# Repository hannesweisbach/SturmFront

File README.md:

# SturmFront

SturmFront is a DIY fan-controller for indoor sports, which adjusts fan speed according to your current heart rate.

Commercially available is the Wahoo® KICKR Headwind, which has an integrated fan and regulates fan speed according to your power output. Keith Wakeham developed an open-source DIY fan controller named [Maelstom](https://github.com/kwakeham/Maelstrom). Maelstrom also adjusts fan speed according to your power output.

I developed SturmFront independently. A project description is also available: [https://hannesweisbach.github.io/SturmFront/](https://hannesweisbach.github.io/SturmFront/)

## Software used

I used KiCAD as EDA-tool. The controller is based on the Nordic Semiconductor [NRF52832 SoC](https://www.nordicsemi.com/products/nrf52832). I used the [NRF5 SDK 17.1.0](https://www.nordicsemi.com/Products/Development-software/nrf5-sdk/download) in conjuction with the [S332 softdevice](https://www.nordicsemi.com/Products/Development-software/s332-ant) to provide ANT+ and BLE connectivity.

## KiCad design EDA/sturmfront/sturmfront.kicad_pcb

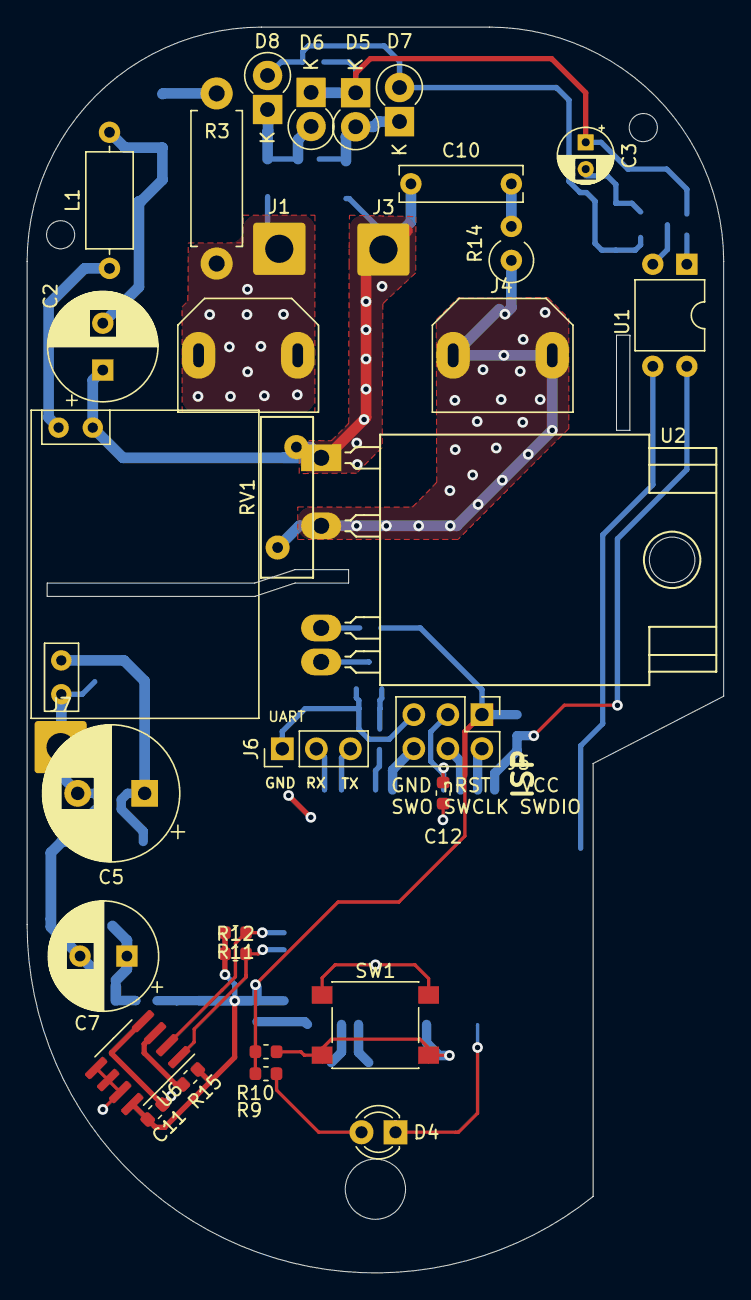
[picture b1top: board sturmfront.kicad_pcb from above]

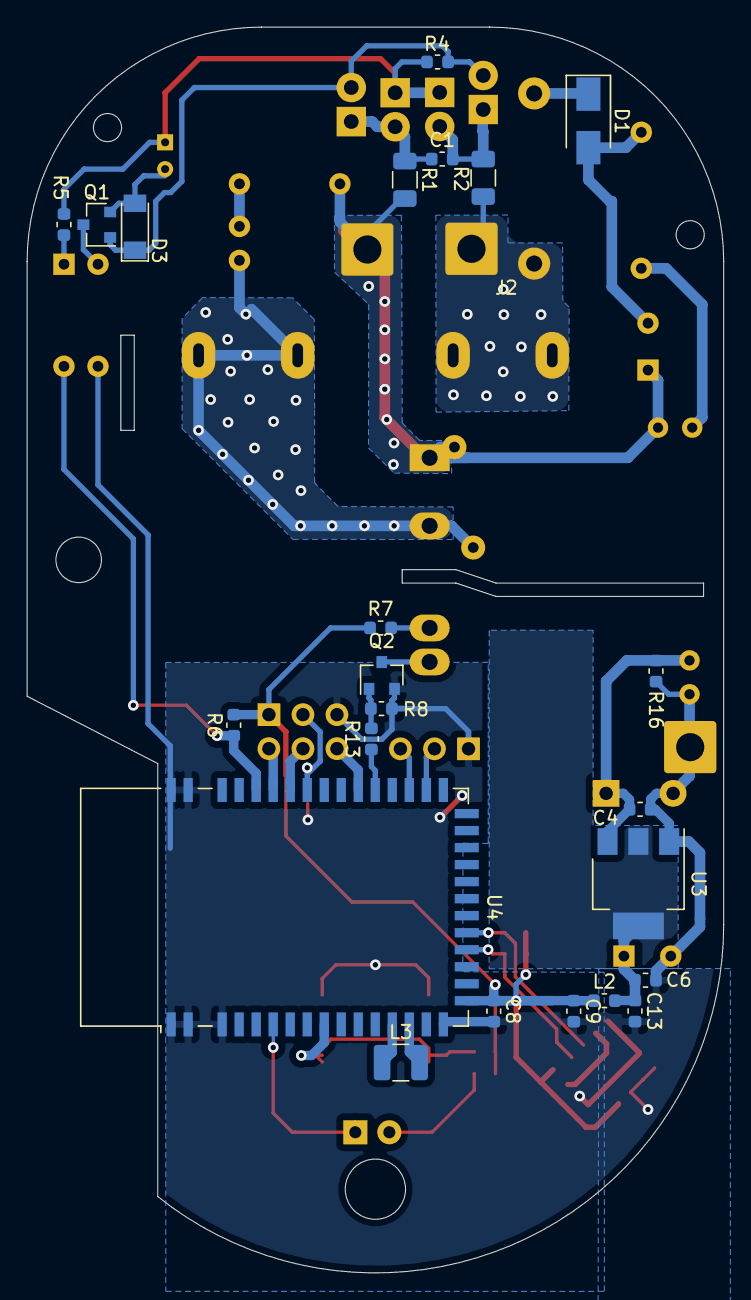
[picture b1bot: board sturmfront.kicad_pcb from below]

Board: 2 copper layers, 52.0 x 93.0 mm, 59 parts (23 on the bottom side), 37 nets.

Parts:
C1: 1nF, 16V; C_0603_1608Metric
C2: CP; CP_Radial_D8.0mm_P3.50mm
C3: 10u, 10V; CP_Radial_D4.0mm_P2.00mm
C4, C6, C8, C9, C11, C13: 100n; C_0603_1608Metric
C5: 470u, 35V; CP_Radial_D10.0mm_P5.00mm
C7: 220u, 16V; CP_Radial_D8.0mm_P3.50mm
C10: 33n, 500V; C_Rect_L9.0mm_W2.5mm_P7.50mm_MKT
C12: 10n; C_0603_1608Metric
D1: D; D_SMA
D3: D; D_MiniMELF
D4: LED; LED_D3.0mm_Clear
D5, D6, D7, D8: 1N4148; D_DO-41_SOD81_P2.54mm_Vertical_KathodeUp
H1: MountingHole; MountingHole_4.5mm
H2, H3: MountingHole; MountingHole_2.1mm
J1: N_IN; SolderWire-1.5sqmm_1x01_D1.7mm_OD3.9mm
J2: N_OUT; PowerSocket
J3: L_IN; SolderWire-1.5sqmm_1x01_D1.7mm_OD3.9mm
J4: L_OUT; PowerSocket
J5: Conn_02x03_Odd_Even; PinHeader_2x03_P2.54mm_Vertical
J6: Conn_01x03; PinHeader_1x03_P2.54mm_Vertical
J7: PE; SolderWire-1.5sqmm_1x01_D1.7mm_OD3.9mm
L1: L; L_Axial_L7.0mm_D3.3mm_P10.16mm_Horizontal_Fastron_MICC
L2: L; L_0603_1608Metric
L3: L; L_1210_3225Metric
PS1: E365041; DCDC
Q1: MBT2222A; SOT-23
Q2: Q_NMOS_DGS; SOT-23
R1, R2: 220k; R_1206_3216Metric
R3: R; R_Axial_DIN0411_L9.9mm_D3.6mm_P12.70mm_Horizontal
R4: 22k; R_0603_1608Metric
R5, R9, R10, R13: 1k; R_0603_1608Metric
R6, R11, R12, R15: 4k7; R_0603_1608Metric
R7: 100; R_0603_1608Metric
R8, R16: 10k; R_0603_1608Metric
R14: 10; R_Axial_DIN0309_L9.0mm_D3.2mm_P2.54mm_Vertical
RV1: 600V, 250VAC; RV_Disc_D12mm_W3.9mm_P7.5mm
SW1: SW_Push_Dual; SW_Push_1P1T_NO_6x6mm_H9.5mm
U1: PC817; DIP-4_W7.62mm
U2: S202S01; SIP4_Sharp-SSR_P7.62mm_Angled
U3: AMS1117-3.3; SOT-223-3_TabPin2
U4: E73-2G4M04S-52832; E73-2G4M04S
U6: LM75B; SOIC-8_3.9x4.9mm_P1.27mm

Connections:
+3V3: C8.1, C9.1, C11.1, J5.1, L2.1, R6.2, R7.1, R9.1, R10.2, R11.2, R12.2, R15.2, U4.16, U6.8
+5VP: C4.1, C5.1, PS1.4, R16.1, U3.3
GND: C4.2, C5.2, C6.2, C7.2, C8.2, C9.2, C11.2, C12.2, C13.2, J5.5, J6.1, J7.1, PS1.3, Q2.2, R8.2, R16.2, SW1.1, U1.3, U3.1, U4.0, U4.1, U4.2, U4.15, U4.42, U4.43, U6.4, U6.5, U6.6, U6.7
LINE: C2.1, C10.1, J3.1, PS1.1, R1.2, RV1.1, U2.1
LOAD_ON: R13.1, U4.32
NEUT: J1.1, J2.1, R2.2, R3.2
unnamed: C1.1, D5.2, D7.1, R1.1
unnamed: C1.2, D6.2, D8.1, R2.1
unnamed: C2.2, D1.2, L1.2
unnamed: C3.1, D5.1, D6.1, R4.2, R5.1
unnamed: C3.2, D3.2, Q1.2
unnamed: C10.2, R14.2
unnamed: C6.1, C7.1, C13.1, L2.2, U3.2
unnamed: D1.1, R3.1
unnamed: D3.1, D7.2, D8.2, Q1.1, R4.1
unnamed: D4.1, U4.5
unnamed: D4.2, R9.2
unnamed: J4.1, R14.1, RV1.2, U2.2
unnamed: L1.1, PS1.2
unnamed: L3.1, U4.12
unnamed: L3.2, U4.13
unnamed: Q1.3, U1.2
unnamed: Q2.1, R8.1, R13.2
unnamed: Q2.3, U2.4
unnamed: R5.2, U1.1
unnamed: R7.2, U2.3
unnamed: R10.1, SW1.2, U4.8
unnamed: R15.1, U6.3
RX: J6.2, U4.29
SCL: R11.1, U4.20, U6.2
SDA: R12.1, U4.19, U6.1
SWCLK: J5.4, U4.37
SWDIO: J5.2, U4.38
SWO: J5.6, U4.33
TX: J6.3, U4.30
ZC: R6.1, U1.4, U4.39
nRST: C12.1, J5.3, U4.36

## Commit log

2022-01-02 Add first description to README.md
2022-01-03 Set theme jekyll-theme-slate
2022-01-03 KiCAD EDA files
2022-01-03 Zerocross oscilloscope screenshots
2022-01-03 Add initial project description
2022-01-11 Add sturmfront schematic
2022-01-11 Initial firmware commit
2022-01-11 Update .gitignore
    Add vim temp files and .DS_Store
2022-01-26 Move github.io files in their own directory
2022-01-26 Add Wifi plug images
2022-01-26 Add wifi socket images
2022-01-26 Add prototyping and PCB images
2022-01-26 Move files back from github.io-subfolder
    Github Pages does not support subdirectories
2022-01-26 Fix quoting error in HTML
2022-01-26 Add image of debugging the engineering prototype
2022-01-26 Add images and description to the Hardware section
2022-01-26 Add PNG of schematic for github pages
2022-01-26 Add circuit description
